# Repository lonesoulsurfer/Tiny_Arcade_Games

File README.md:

Tiny Arcade Games

*Parts list can be found in the Instructables link below*

I've recently taken the leap into playing around with microcontrollers, specifically the 8 bit ATtiny85 and so far it's been a blast!

The games available are your classic arcade games like Frogger, Space Attack, Breakout, Snake, Pong, and others. It still blows my mind that you can fit a whole game into one of these tiny IC's!

For those new to ATtiny microcontrollers, It is a small, integrated, 8 pin IC, similar to the Arduino, but with much less IO pins, smaller memory and a smaller form factor. Don't let the smallness of the IC fool you, ATtiny85 microcontroller can perform a whole bunch of different functions on a single IC once it has been programmed. In this project we will be programming it with some arcade games.

Don't worry if you a totally new to all of this. I have created this project with beginners in mind so if you have some basic soldering skills and a computer you shouldn't have any issues building your own. I've used through hole components and off-the-shelf parts which you can buy cheaply from Ali-Express etc.

I've published a repository in GutHub on how to program an ATtiny 85 which you can find here: https://github.com/lonesoulsurfer/ATtiny_85_Programmer  

Here is a video of the games in action: https://www.youtube.com/watch?v=dKiPz_Yv8tA&feature=youtu.be

I've also published an Instructable which you can find here: https://www.instructables.com/Tiny-Arcade-Game-Attiny85/

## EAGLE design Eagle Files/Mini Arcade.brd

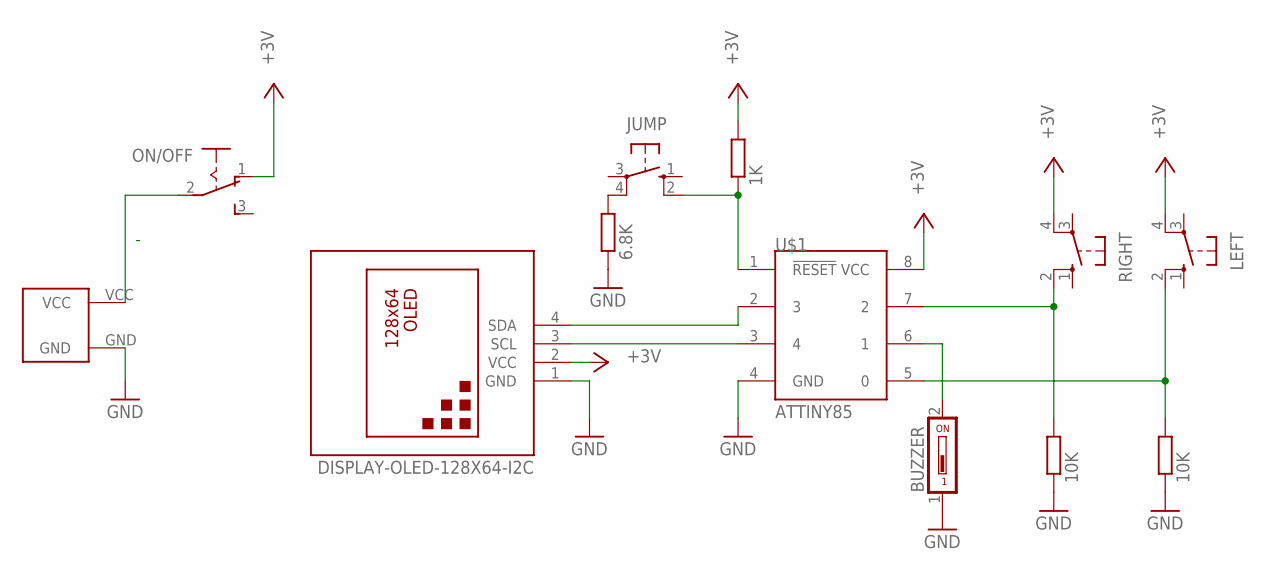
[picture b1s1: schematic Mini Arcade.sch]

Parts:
BUZZER: DS01; DS-01
JUMP: 10-XX; B3F-10XX
LEFT: 10-XX; B3F-10XX
ON/OFF: M251
R1, R2: 10K; 0207/10
R3: 1K; 0207/10
R4: 6.8K; 0207/10
RIGHT: 10-XX; B3F-10XX
U$1: ATTINY85; 8P3
U$2: DISPLAY-OLED-128X64-I2C
U$5: CR2032; CR2032-20MM

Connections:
+3V3: LEFT.4 (P1), ON/OFF.1 (O), R3.2, RIGHT.4 (P1), U$1.8 (VCC), U$2.2 (VCC)
GND: BUZZER.1, R1.1, R2.1, R4.1, U$1.4 (GND), U$2.1 (GND), U$5.GND
unnamed: U$1.3 (4), U$2.3 (SCL)
unnamed: U$1.2 (3), U$2.4 (SDA)
unnamed: R1.2, RIGHT.2 (S1), U$1.7 (2)
unnamed: LEFT.2 (S1), R2.2, U$1.5 (0)
unnamed: BUZZER.2, U$1.6 (1)
unnamed: JUMP.4 (P1), R4.2
unnamed: JUMP.2 (S1), R3.1, U$1.1 (!RESET)
unnamed: ON/OFF.2, U$5.VCC

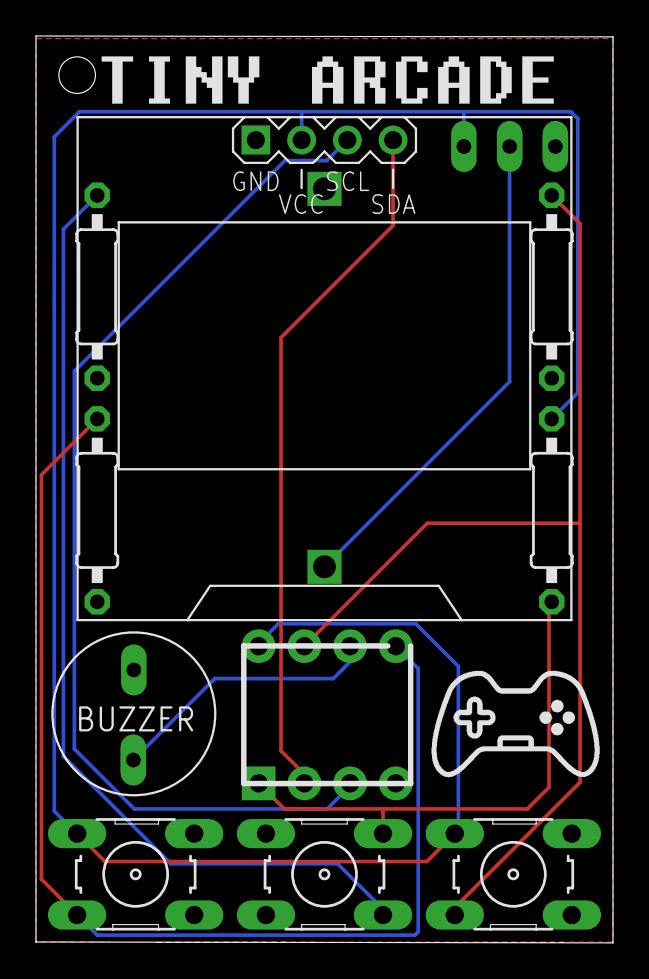
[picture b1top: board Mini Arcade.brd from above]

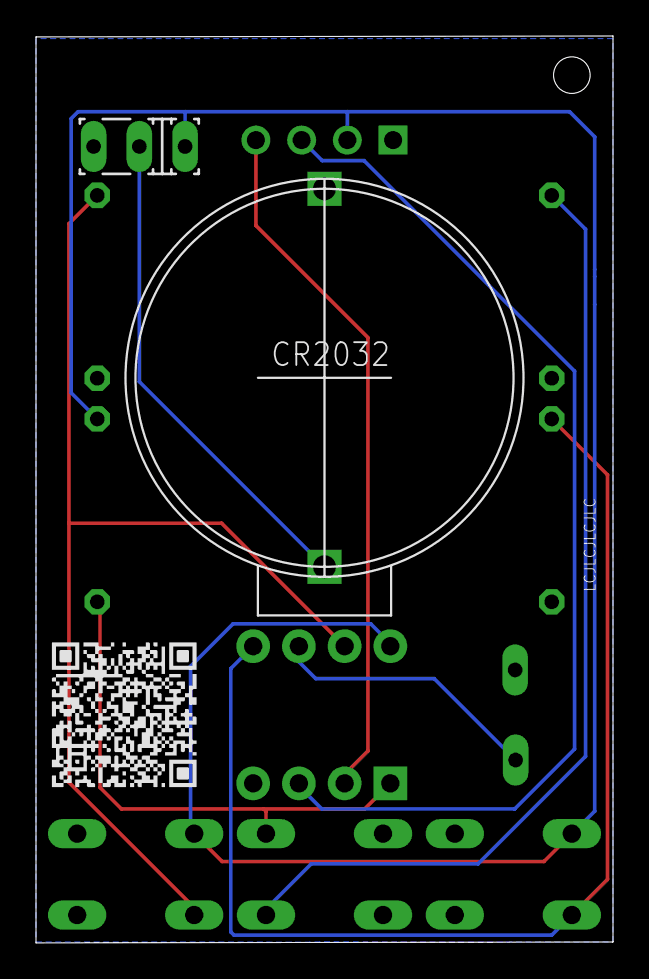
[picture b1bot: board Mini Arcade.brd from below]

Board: 2 copper layers, 32.1 x 50.4 mm, 12 parts (2 on the bottom side), 10 nets.

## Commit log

2024-12-26 File Upload

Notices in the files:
parts and their libraries:
diy-modules: Released under the Creative Commons Attribution 4.0 International License: http://creativecommons.org/licenses/by/4.0
